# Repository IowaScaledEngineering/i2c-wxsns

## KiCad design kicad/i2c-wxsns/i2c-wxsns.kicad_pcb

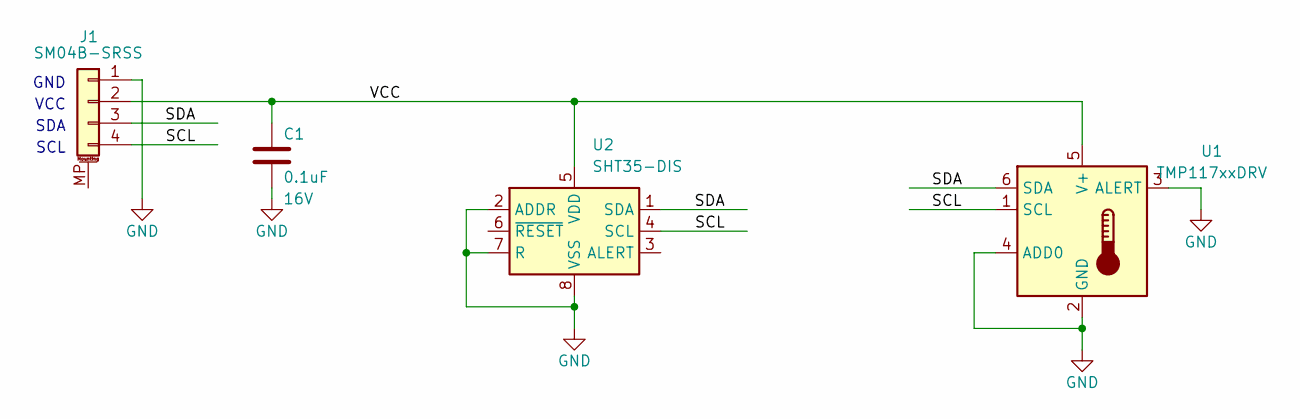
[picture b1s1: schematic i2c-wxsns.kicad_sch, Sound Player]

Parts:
C1: 0.1uF; C_0805_2012Metric; Voltage 16V
J1: SM04B-SRSS; JST_SH_SM04B-SRSS-TB_1x04-1MP_P1.00mm_Horizontal
U1: TMP117xxDRV; WSON-6-1EP_2x2mm_P0.65mm_EP1x1.6mm
U2: SHT35-DIS; Sensirion_DFN-8-1EP_2.5x2.5mm_P0.5mm_EP1.1x1.7mm

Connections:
/SCL: J1.4, U1.1 (SCL), U2.4 (SCL)
/SDA: J1.3, U1.6 (SDA), U2.1 (SDA)
/VCC: C1.1, J1.2, U1.5 (V+), U2.5 (VDD)
GND: C1.2, J1.1, U1.2 (GND), U1.3 (ALERT), U1.4 (ADD0), U2.2 (ADDR), U2.7 (R), U2.8 (VSS), U2.9 (VSS)

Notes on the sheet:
SDA
GND
VCC
SCL

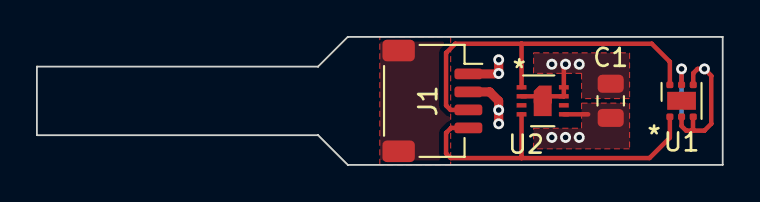
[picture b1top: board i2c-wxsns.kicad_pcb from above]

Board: 2 copper layers, 38.1 x 7.1 mm, 4 parts (0 on the bottom side), 4 nets.

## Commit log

2016-01-30 Changed wire connector spacing to 60mil
2016-01-30 Sent to fab 1/29/2016
2018-11-27 v2 PCB
2018-11-27 Added metal pad under connector
2018-11-29 Updated to use TMP117
2019-11-09 v2.1 files
2019-11-09 Indirectly connected U1's ground pins (not to center pad) to avoid solder flow onto enter pad due to thin (non-existent) solder mask. Added stencil attachment tab to panel.
2019-12-14 v2.2 fab files
2019-12-16 Added dummy footprint to backside to make PCBWay happy (no bottom soldermask otherwise).
2019-12-16 File for fab
2020-07-13 Source code for the sensor
2020-08-25 Packet format updates
2020-08-25 Fixed tmp117 I2C transactions
2020-08-26 Fixed CRC calculation
2020-09-05 Other datasheets
2020-09-05 Solar calculations
2020-09-05 File for weather shield
2021-05-31 Additional mechanical bits
2021-05-31 Fix toWDT timer (ported from MRBW-TH project)
2021-05-31 Firmware image with WDT change
2021-05-31 Added firmware target
2023-06-12 Added app note
2023-06-12 v3 files
2023-06-12 .gitignore file
2023-06-22 Fixed DRC
2023-06-28 Sent to fab June 2023

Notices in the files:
kicad/i2c-wxsns/i2c-wxsns.kicad_pcb:
CC BY-SA
©2023
